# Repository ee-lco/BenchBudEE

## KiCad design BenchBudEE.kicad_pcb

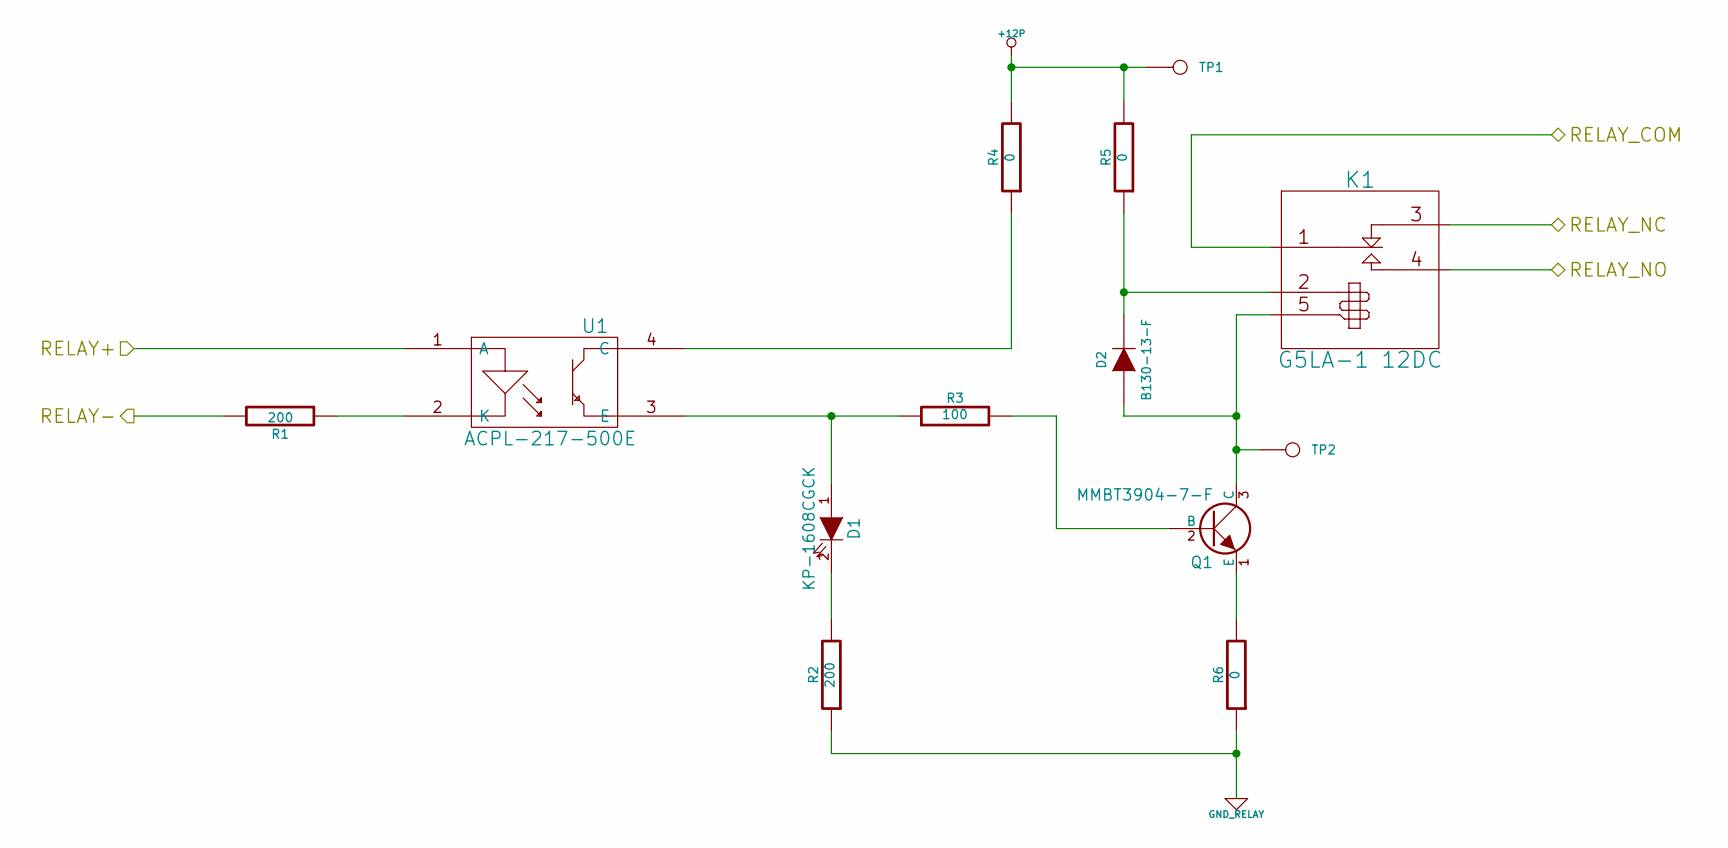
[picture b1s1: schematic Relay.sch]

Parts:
D1: KP-1608CGCK; LED-0603
D2: B130-13-F; Diode-SMA_Standard
K1: G5LA-1 12DC; TE-SPDT
Q1: MMBT3904-7-F; SOT23EBC; MFG Part Number MMBT3904-7-F
R1, R2: 200; SM0805
R3: 100; SM0805
R4, R5, R6: 0; SM0805
TP1: +12P; TestPointTH
TP2: RLY_LOW; TestPointTH
U1: ACPL-217-500E; 4-SMD; MFG Part Number LTV-816S

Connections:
+12P: R4.2, R5.2, TP1.1; also elsewhere on the board
/Arduino/RELAY+: U1.1 (A); also elsewhere on the board
/Arduino/RELAY-: R1.2; also elsewhere on the board
/Relay/RELAY_COM: K1.1 (COM); also elsewhere on the board
/Relay/RELAY_NC: K1.3 (NC); also elsewhere on the board
/Relay/RELAY_NO: K1.4 (NO); also elsewhere on the board
GND_RELAY: R2.1, R6.1; also elsewhere on the board
unnamed: D1.1 (A), R3.1, U1.3 (E)
unnamed: D1.2 (K), R2.2
unnamed: D2.1 (A), K1.5 (COIL-), Q1.3 (C), TP2.1
unnamed: D2.2 (K), K1.2 (COIL+), R5.1
unnamed: Q1.1 (E), R6.2
unnamed: Q1.2 (B), R3.2
unnamed: R1.1, U1.2 (K)
unnamed: R4.1, U1.4 (C)

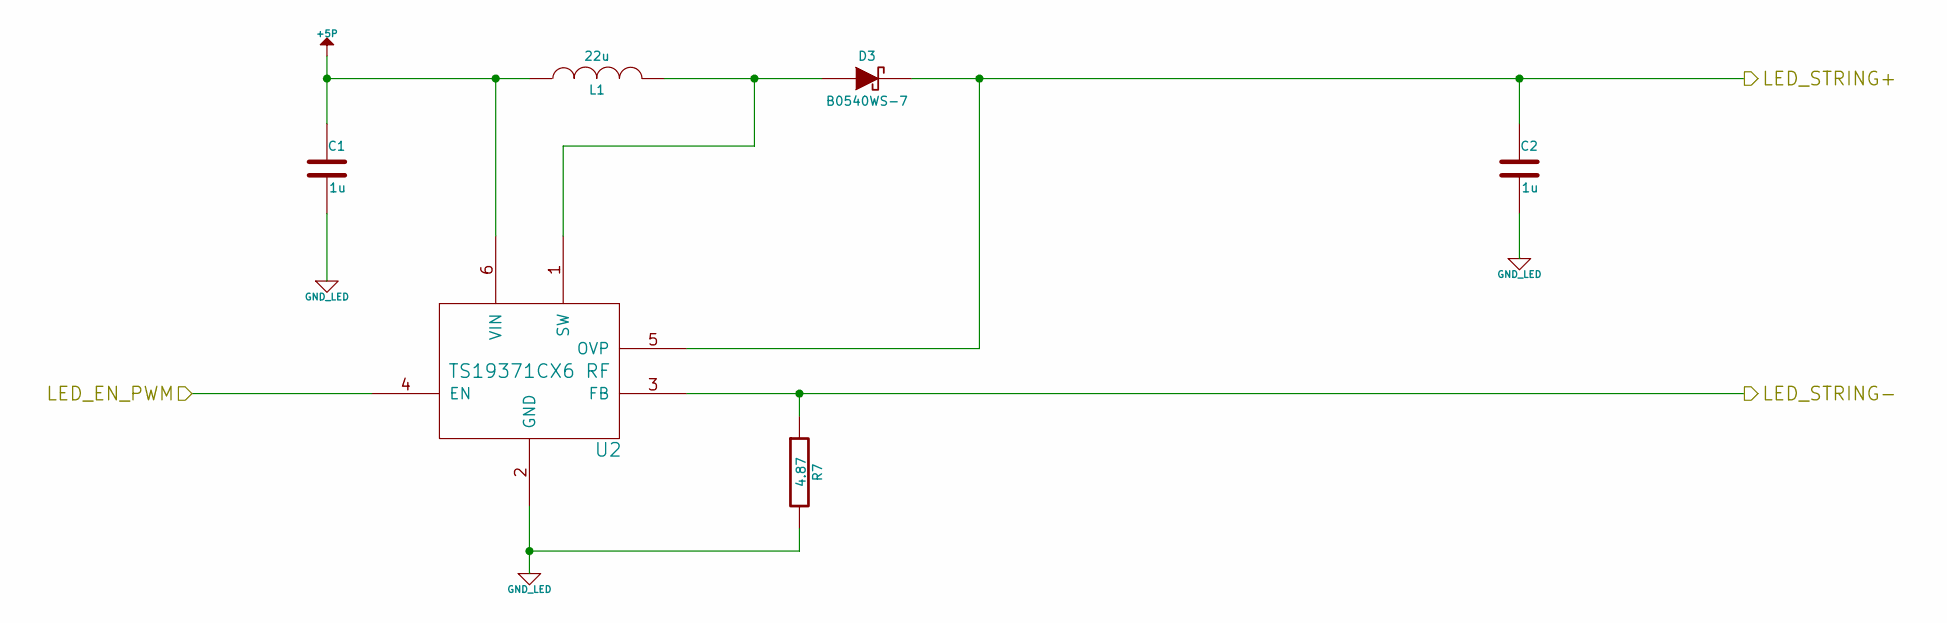
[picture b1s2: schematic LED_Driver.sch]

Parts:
C1, C2: 1u; c_0805
D3: B0540WS-7; SOD-323; MFG Part Number BO540WS-7
L1: 22u; NR4012; MFG Part Number NR4012T220M
R7: 4.87; SM0805
U2: TS19371CX6 RF; SOT23_6

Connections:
+5P: C1.1, L1.1, U2.6 (VIN); also elsewhere on the board
/Arduino/LED_EN_PWM: U2.4 (EN); also elsewhere on the board
/LED_Driver/LED_STRING+: C2.1, D3.2 (K), U2.5 (OVP); also elsewhere on the board
/LED_Driver/LED_STRING-: R7.1, U2.3 (FB); also elsewhere on the board
GND_LED: C1.2, C2.2, R7.2, U2.2 (GND); also elsewhere on the board
unnamed: D3.1 (A), L1.2, U2.1 (SW)

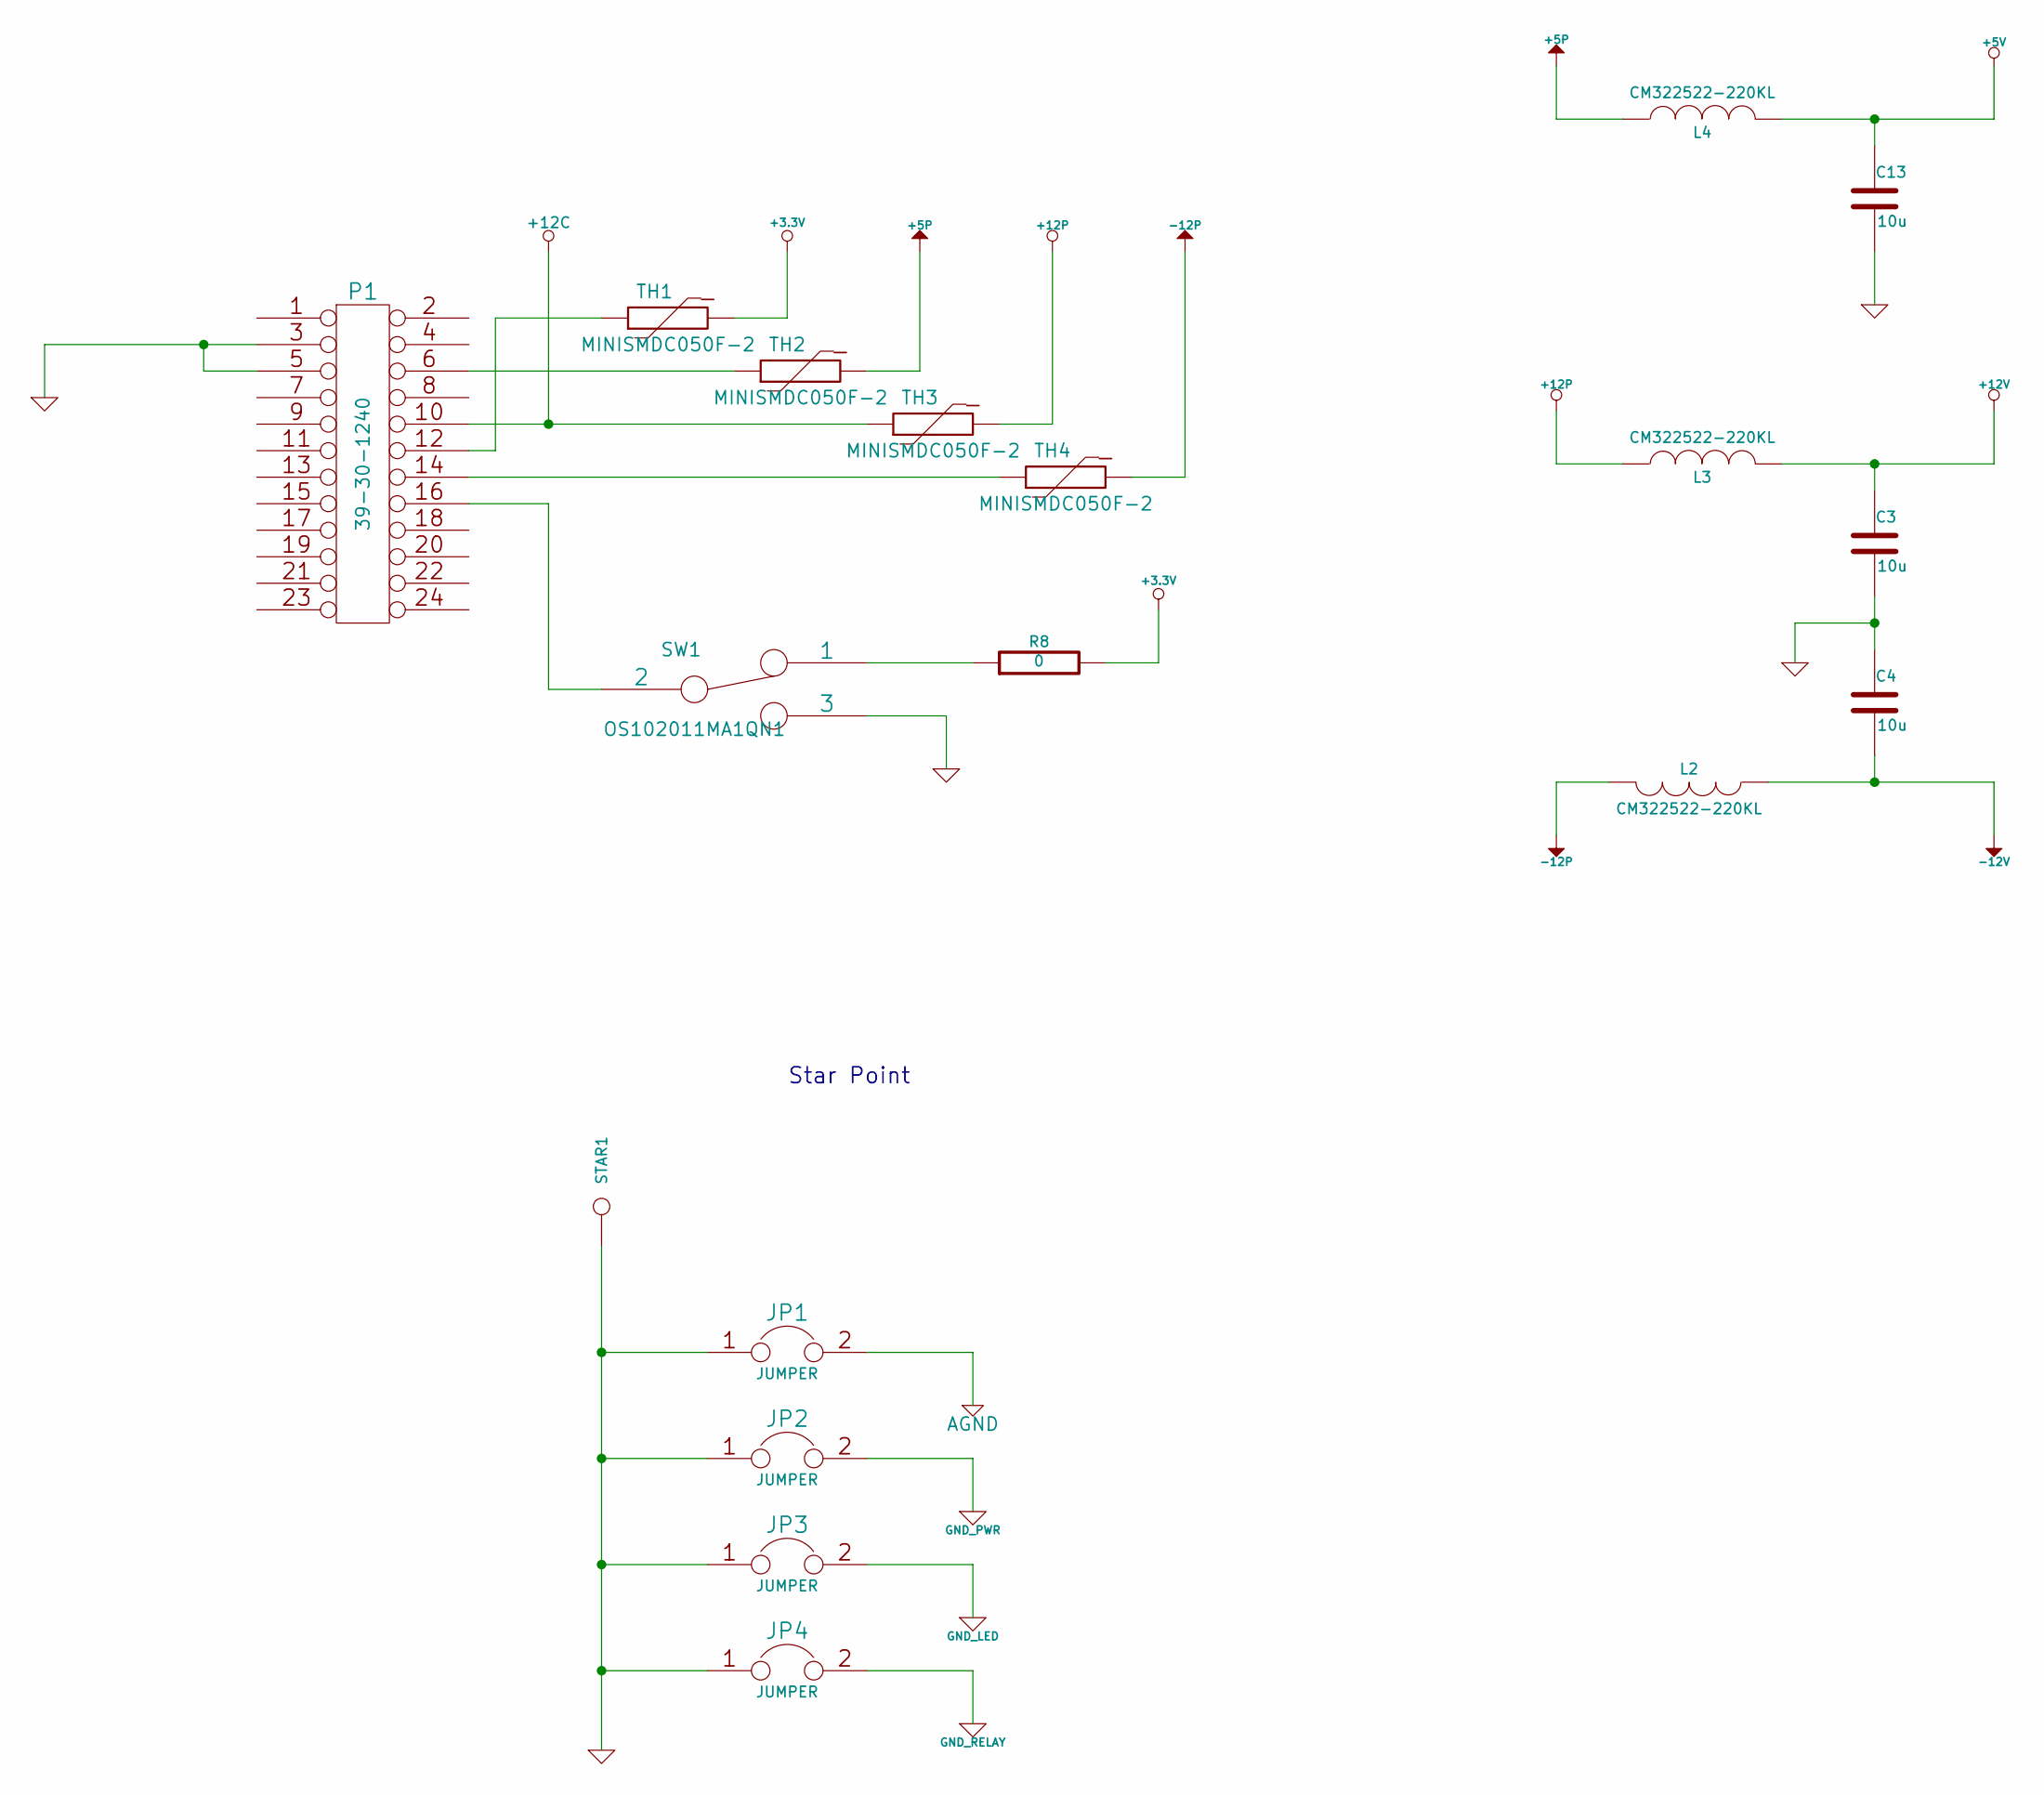
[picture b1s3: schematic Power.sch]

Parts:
C3, C4, C13: 10u; c_1206
JP1, JP2, JP3, JP4: JUMPER; GND_POINT
L2, L3, L4: CM322522-220KL; SM1210L
P1: 39-30-1240; ATX_Header; MFG Part Number 39-30-1240
R8: 0; SM0805
STAR1: CONN_1; 1pin
SW1: OS102011MA1QN1; BB_switch; MFG Part Number OS102011MA1QN1
TH1, TH2, TH3, TH4: MINISMDC050F-2; SM1812; MFG Part Number MINISMDC050F-2

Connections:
+3.3V: R8.2, TH1.2; also elsewhere on the board
+5P: L4.1, TH2.2; also elsewhere on the board
+5V: C13.1, L4.2; also elsewhere on the board
+12C: P1.10, TH3.1; also elsewhere on the board
+12P: L3.1, TH3.2; also elsewhere on the board
+12V: C3.1, L3.2; also elsewhere on the board
-12P: L2.2, TH4.2
-12V: C4.2, L2.1; also elsewhere on the board
AGND: JP1.2; also elsewhere on the board
GND: C3.2, C4.1, C13.2, JP1.1, JP2.1, JP3.1, JP4.1, P1.3, P1.5, STAR1.1, SW1.3; also elsewhere on the board
GND_LED: JP3.2; also elsewhere on the board
GND_PWR: JP2.2; also elsewhere on the board
GND_RELAY: JP4.2; also elsewhere on the board
unnamed: P1.6, TH2.1
unnamed: P1.12, TH1.1
unnamed: P1.14, TH4.1
unnamed: P1.16, SW1.2
unnamed: R8.1, SW1.1

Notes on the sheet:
Star Point

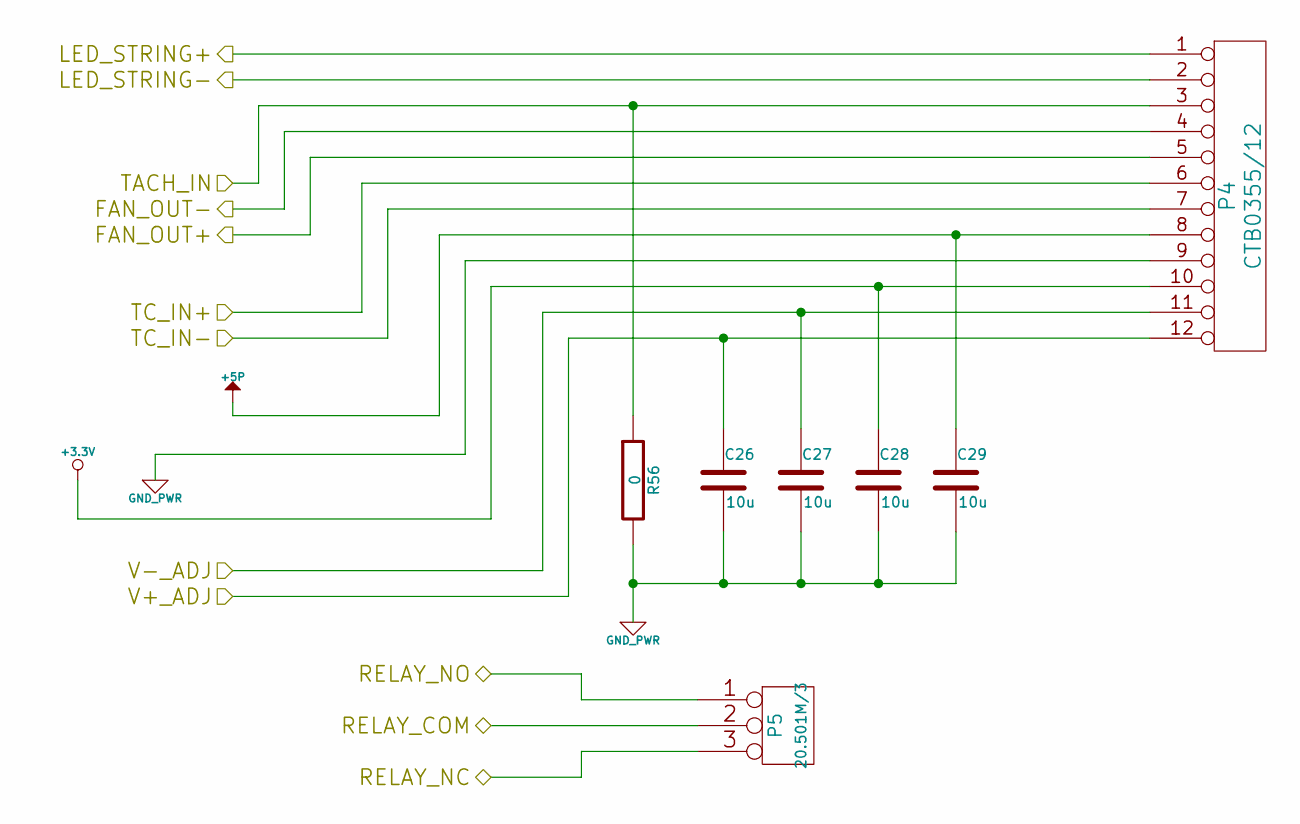
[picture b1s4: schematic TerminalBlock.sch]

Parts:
C26, C27, C28, C29: 10u; c_1210
P4: CTB0355/12; 12pinTB; MFG Part Number OSTTE120104
P5: 20.501M/3; 3pinTB; MFG Part Number 1935174
R56: 0; SM0805

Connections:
+3.3V: C28.1, P4.10; also elsewhere on the board
+5P: C29.1, P4.8; also elsewhere on the board
/Fan/FAN_OUT+: P4.5; also elsewhere on the board
/Fan/FAN_OUT-: P4.4; also elsewhere on the board
/Fan/TACH_IN: P4.3, R56.1; also elsewhere on the board
/LED_Driver/LED_STRING+: P4.1; also elsewhere on the board
/LED_Driver/LED_STRING-: P4.2; also elsewhere on the board
/PowerAdjustmentMonitor/V+_ADJ: C26.1, P4.12; also elsewhere on the board
/PowerAdjustmentMonitor/V-_ADJ: C27.1, P4.11; also elsewhere on the board
/Relay/RELAY_COM: P5.2 (PM); also elsewhere on the board
/Relay/RELAY_NC: P5.3; also elsewhere on the board
/Relay/RELAY_NO: P5.1; also elsewhere on the board
/TerminalBlock/TC_IN+: P4.6; also elsewhere on the board
/TerminalBlock/TC_IN-: P4.7; also elsewhere on the board
GND_PWR: C26.2, C27.2, C28.2, C29.2, P4.9, R56.2; also elsewhere on the board

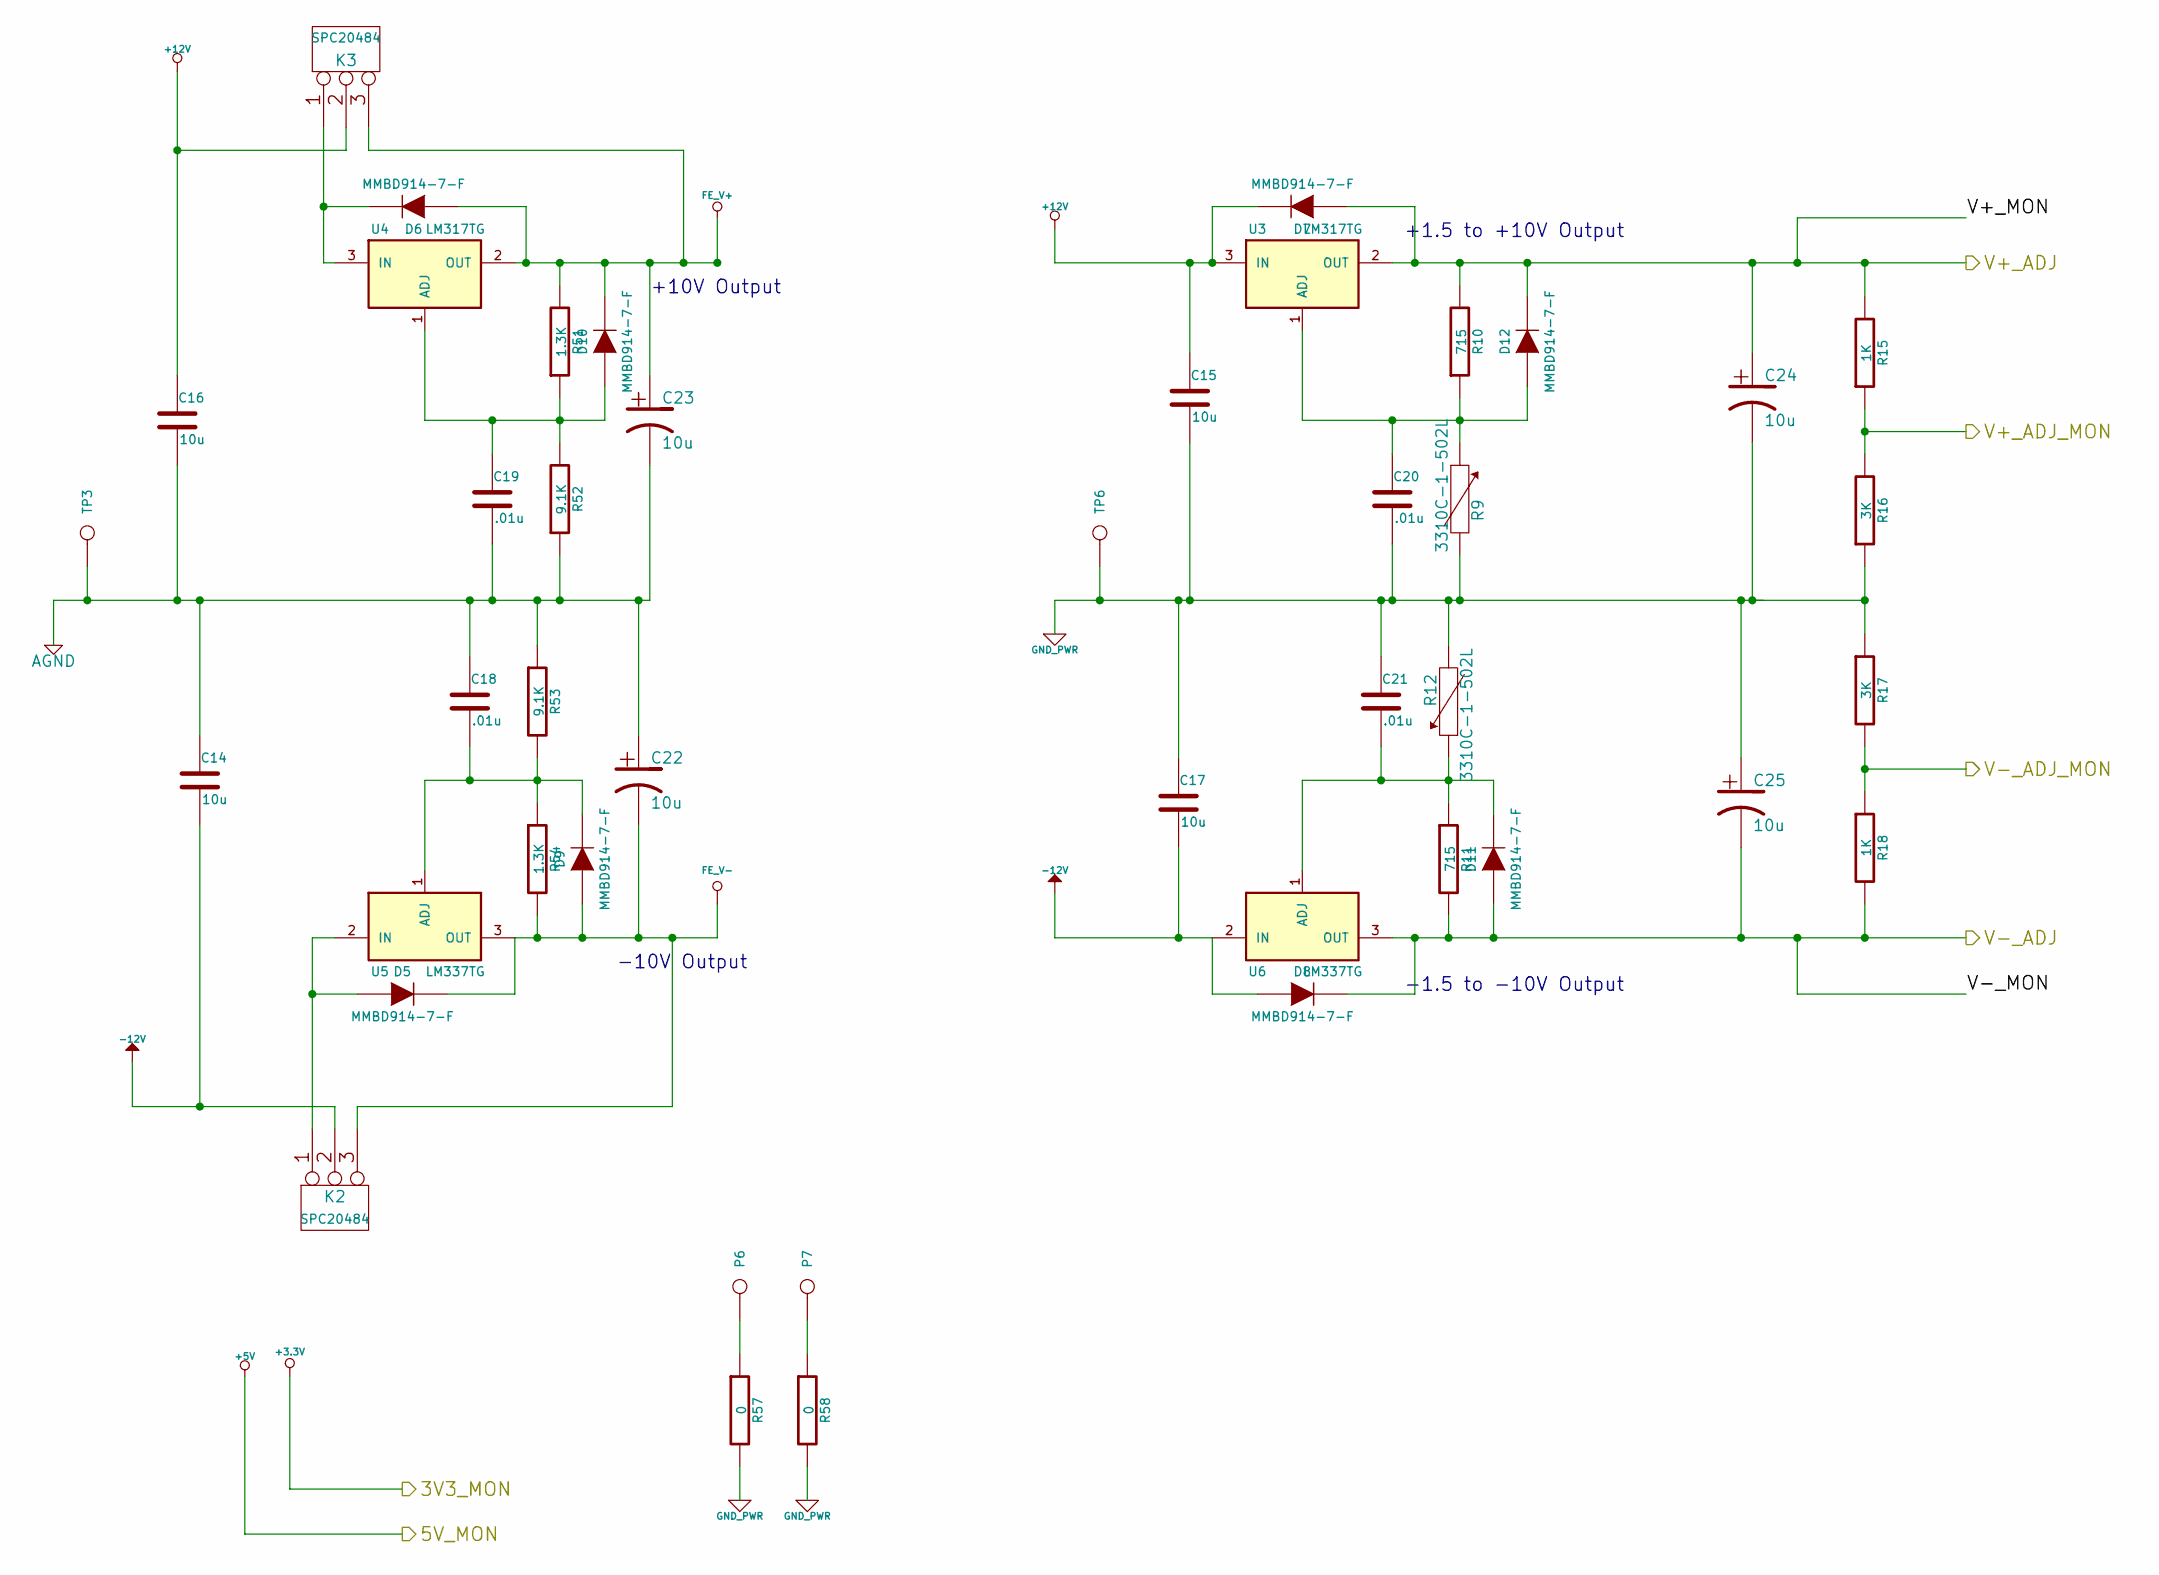
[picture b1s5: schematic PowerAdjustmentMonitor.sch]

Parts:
C14, C15, C16, C17, C22, C23, C24, C25: 10u; c_0805
C18, C19, C20, C21: .01u; c_0805
D5, D6, D7, D8, D9, D10, D11, D12: MMBD914-7-F; SOT23-DIODE; MFG Part Number MMBD914-7-F
K2, K3: SPC20484; Pin_Header_Straight_1x03
P6, P7: MC33282; V8508H
R9, R12: 3310C-1-502L; EVUE3K
R10, R11: 715; SM0805
R15, R18: 1K; SM0805
R16, R17: 3K; SM0805
R51, R54: 1.3K; SM0805
R52, R53: 9.1K; SM0805
R57, R58: 0; SM0805
TP3: AGND; TestPointTH
TP6: GND_PWR; TestPointTH
U3, U4: LM317TG; TO-220_Neutral123_Vertical
U5, U6: LM337TG; TO-220_Neutral123_Vertical

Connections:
+12V: C15.1, C16.1, D7.2 (K), K3.2 (PM), U3.3 (IN); also elsewhere on the board
-12V: C14.2, C17.2, D8.1 (A), K2.2 (PM), U6.2 (IN); also elsewhere on the board
/Arduino/V+_ADJ_MON: R15.1, R16.2; also elsewhere on the board
/Arduino/V-_ADJ_MON: R17.2, R18.1; also elsewhere on the board
/PowerAdjustmentMonitor/V+_ADJ: C24.1, D7.1 (A), D12.2 (K), R10.2, R15.2, U3.2 (OUT); also elsewhere on the board
/PowerAdjustmentMonitor/V-_ADJ: C25.2, D8.2 (K), D11.1 (A), R11.2, R18.2, U6.3 (OUT); also elsewhere on the board
AGND: C14.1, C16.2, C18.1, C19.2, C22.1, C23.2, R52.1, R53.1, TP3.1; also elsewhere on the board
FE_V+: C23.1, D6.1 (A), D10.2 (K), K3.3, R51.2, U4.2 (OUT); also elsewhere on the board
FE_V-: C22.2, D5.2 (K), D9.1 (A), K2.3, R54.2, U5.3 (OUT); also elsewhere on the board
GND_PWR: C15.2, C17.1, C20.2, C21.1, C24.2, C25.1, R9.2, R12.2, R16.1, R17.1, R57.2, R58.2, TP6.1; also elsewhere on the board
unnamed: C18.2, D9.2 (K), R53.2, R54.1, U5.1 (ADJ)
unnamed: C19.1, D10.1 (A), R51.1, R52.2, U4.1 (ADJ)
unnamed: C20.1, D12.1 (A), R9.1, R10.1, U3.1 (ADJ)
unnamed: C21.2, D11.2 (K), R11.1, R12.1, U6.1 (ADJ)
unnamed: D5.1 (A), K2.1, U5.2 (IN)
unnamed: D6.2 (K), K3.1, U4.3 (IN)
unnamed: P6.1, R57.1
unnamed: P7.1, R58.1

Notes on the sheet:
+10V Output
+1.5 to +10V Output
-1.5 to -10V Output
-10V Output

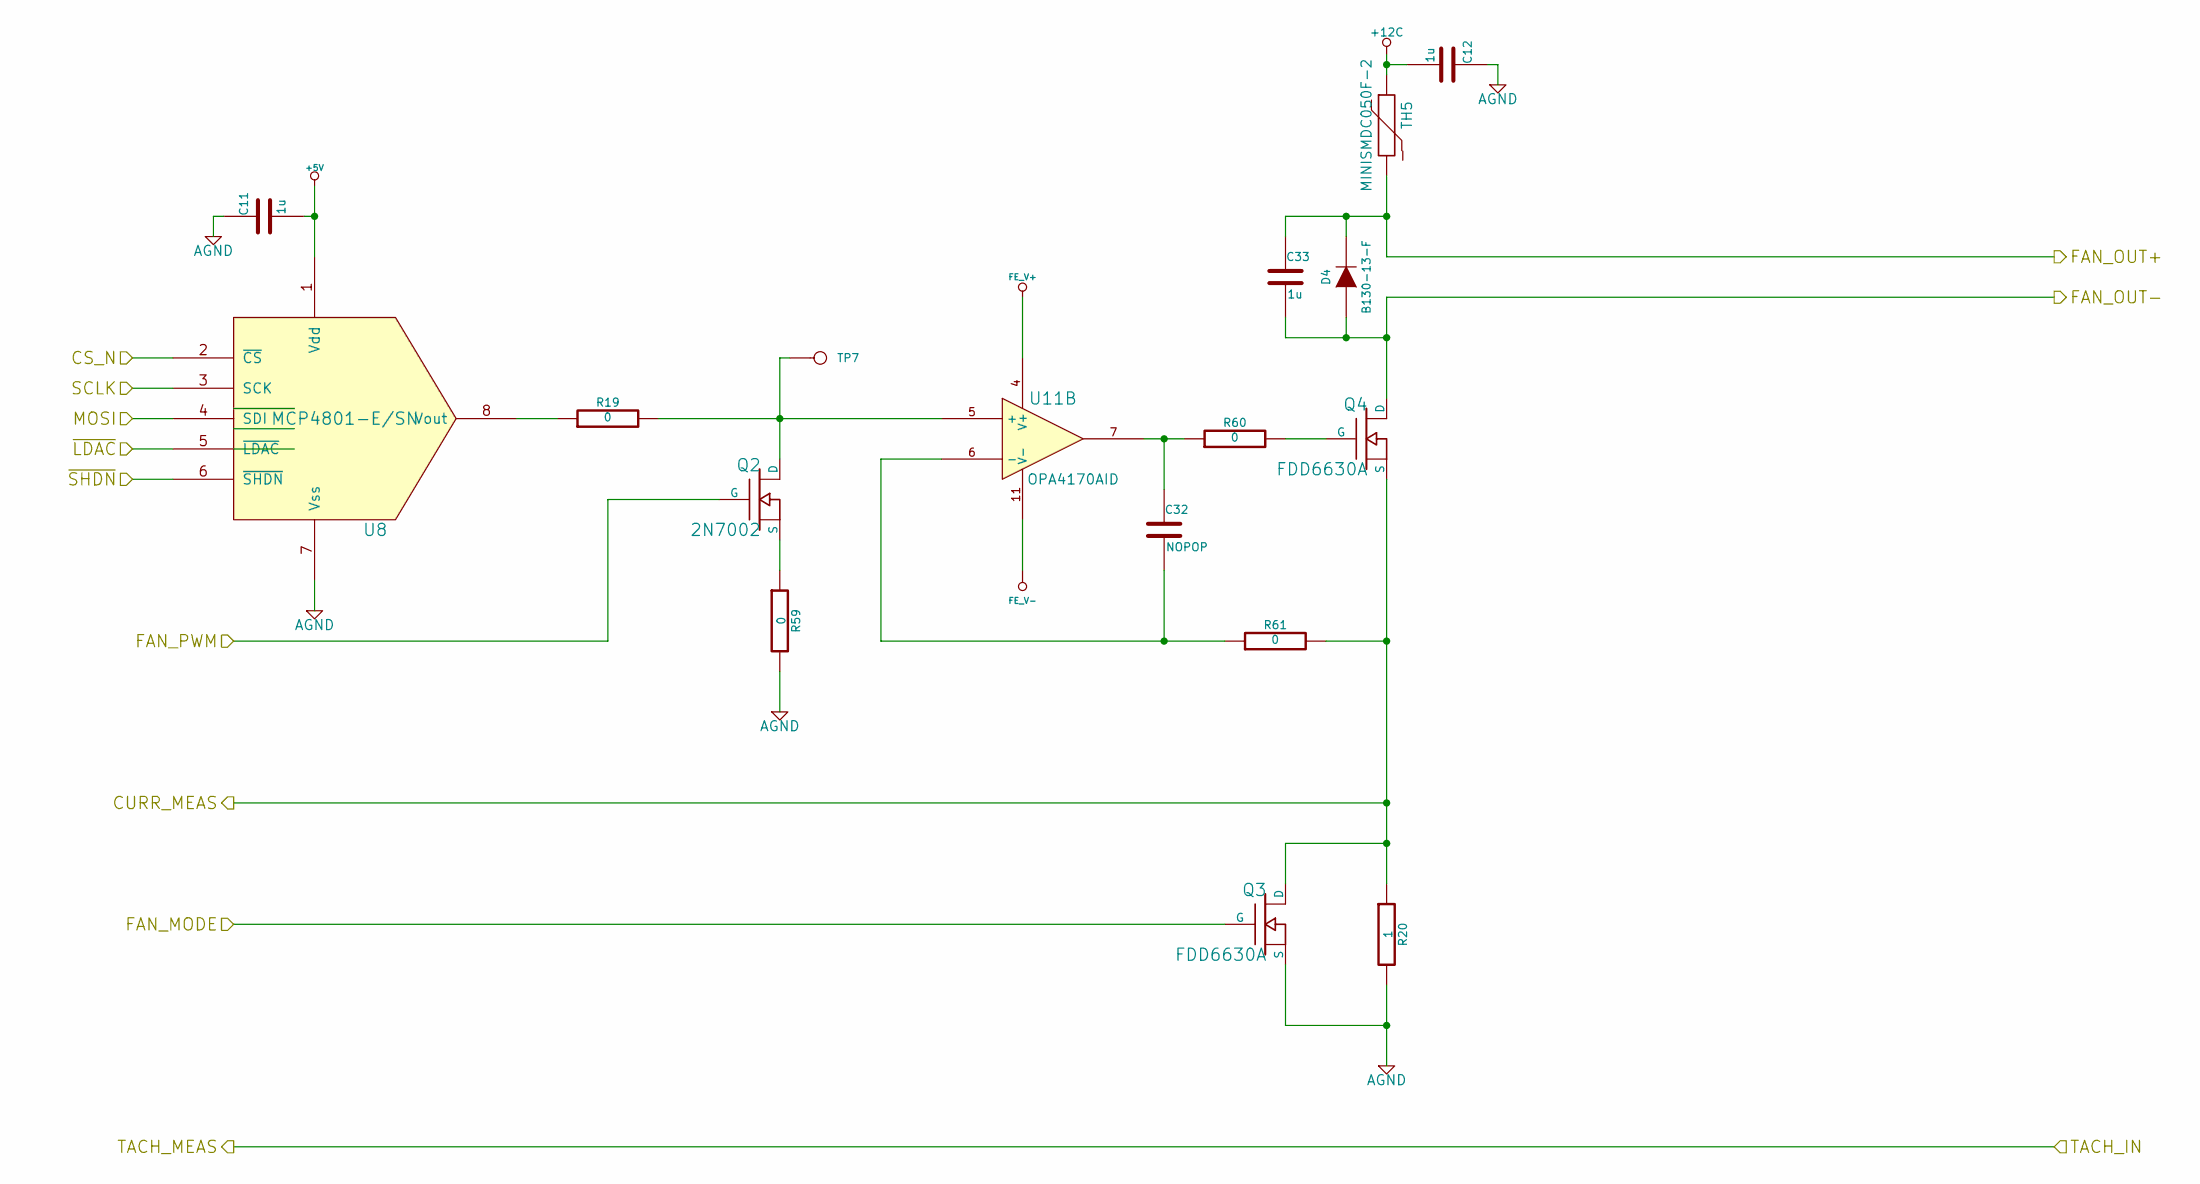
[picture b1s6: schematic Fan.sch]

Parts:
C11, C12, C33: 1u; c_0805
C32: NOPOP; c_0805
D4: B130-13-F; Diode-SMA_Standard; MFG Part Number B130-13-F
Q2: 2N7002; SOT23EBC; MFG Part Number DMN65D8L-7
Q3, Q4: FDD6630A; DPAK2; MFG Part Number AOD476
R19, R59, R60, R61: 0; SM0805
R20: 1; SM1206
TH5: MINISMDC050F-2; SM1812; MFG Part Number MINISMDC050F-2
TP7: DAC_OUT; TestPointTH
U8: MCP4801-E/SN; SO8N
U11: OPA4170AID; SO14E

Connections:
+5V: C11.2, U8.1 (Vdd); also elsewhere on the board
+12C: C12.2, TH5.1; also elsewhere on the board
/Arduino/CURR_MEAS: Q3.2 (D), Q4.3 (S), R20.1, R61.2; also elsewhere on the board
/Arduino/FAN_MODE: Q3.1 (G); also elsewhere on the board
/Arduino/FAN_PWM: Q2.1 (G); also elsewhere on the board
/Arduino/MOSI: U8.4 (SDI); also elsewhere on the board
/Arduino/SCLK: U8.3 (SCK); also elsewhere on the board
/Arduino/~LDAC: U8.5 (~LDAC); also elsewhere on the board
/Arduino/~SHDN: U8.6 (~SHDN); also elsewhere on the board
/Fan/CS_N: U8.2 (~CS); also elsewhere on the board
/Fan/FAN_OUT+: C33.1, D4.2 (K), TH5.2; also elsewhere on the board
/Fan/FAN_OUT-: C33.2, D4.1 (A), Q4.2 (D); also elsewhere on the board
AGND: C11.1, C12.1, Q3.3 (S), R20.2, R59.2, U8.7 (Vss); also elsewhere on the board
FE_V+: U11.4 (V+); also elsewhere on the board
FE_V-: U11.11 (V-); also elsewhere on the board
unnamed: C32.1, R60.1, U11.7
unnamed: C32.2, R61.1, U11.6 (-)
unnamed: Q2.2 (D), R19.2, TP7.1, U11.5 (+)
unnamed: Q2.3 (S), R59.1
unnamed: Q4.1 (G), R60.2
unnamed: R19.1, U8.8 (Vout)

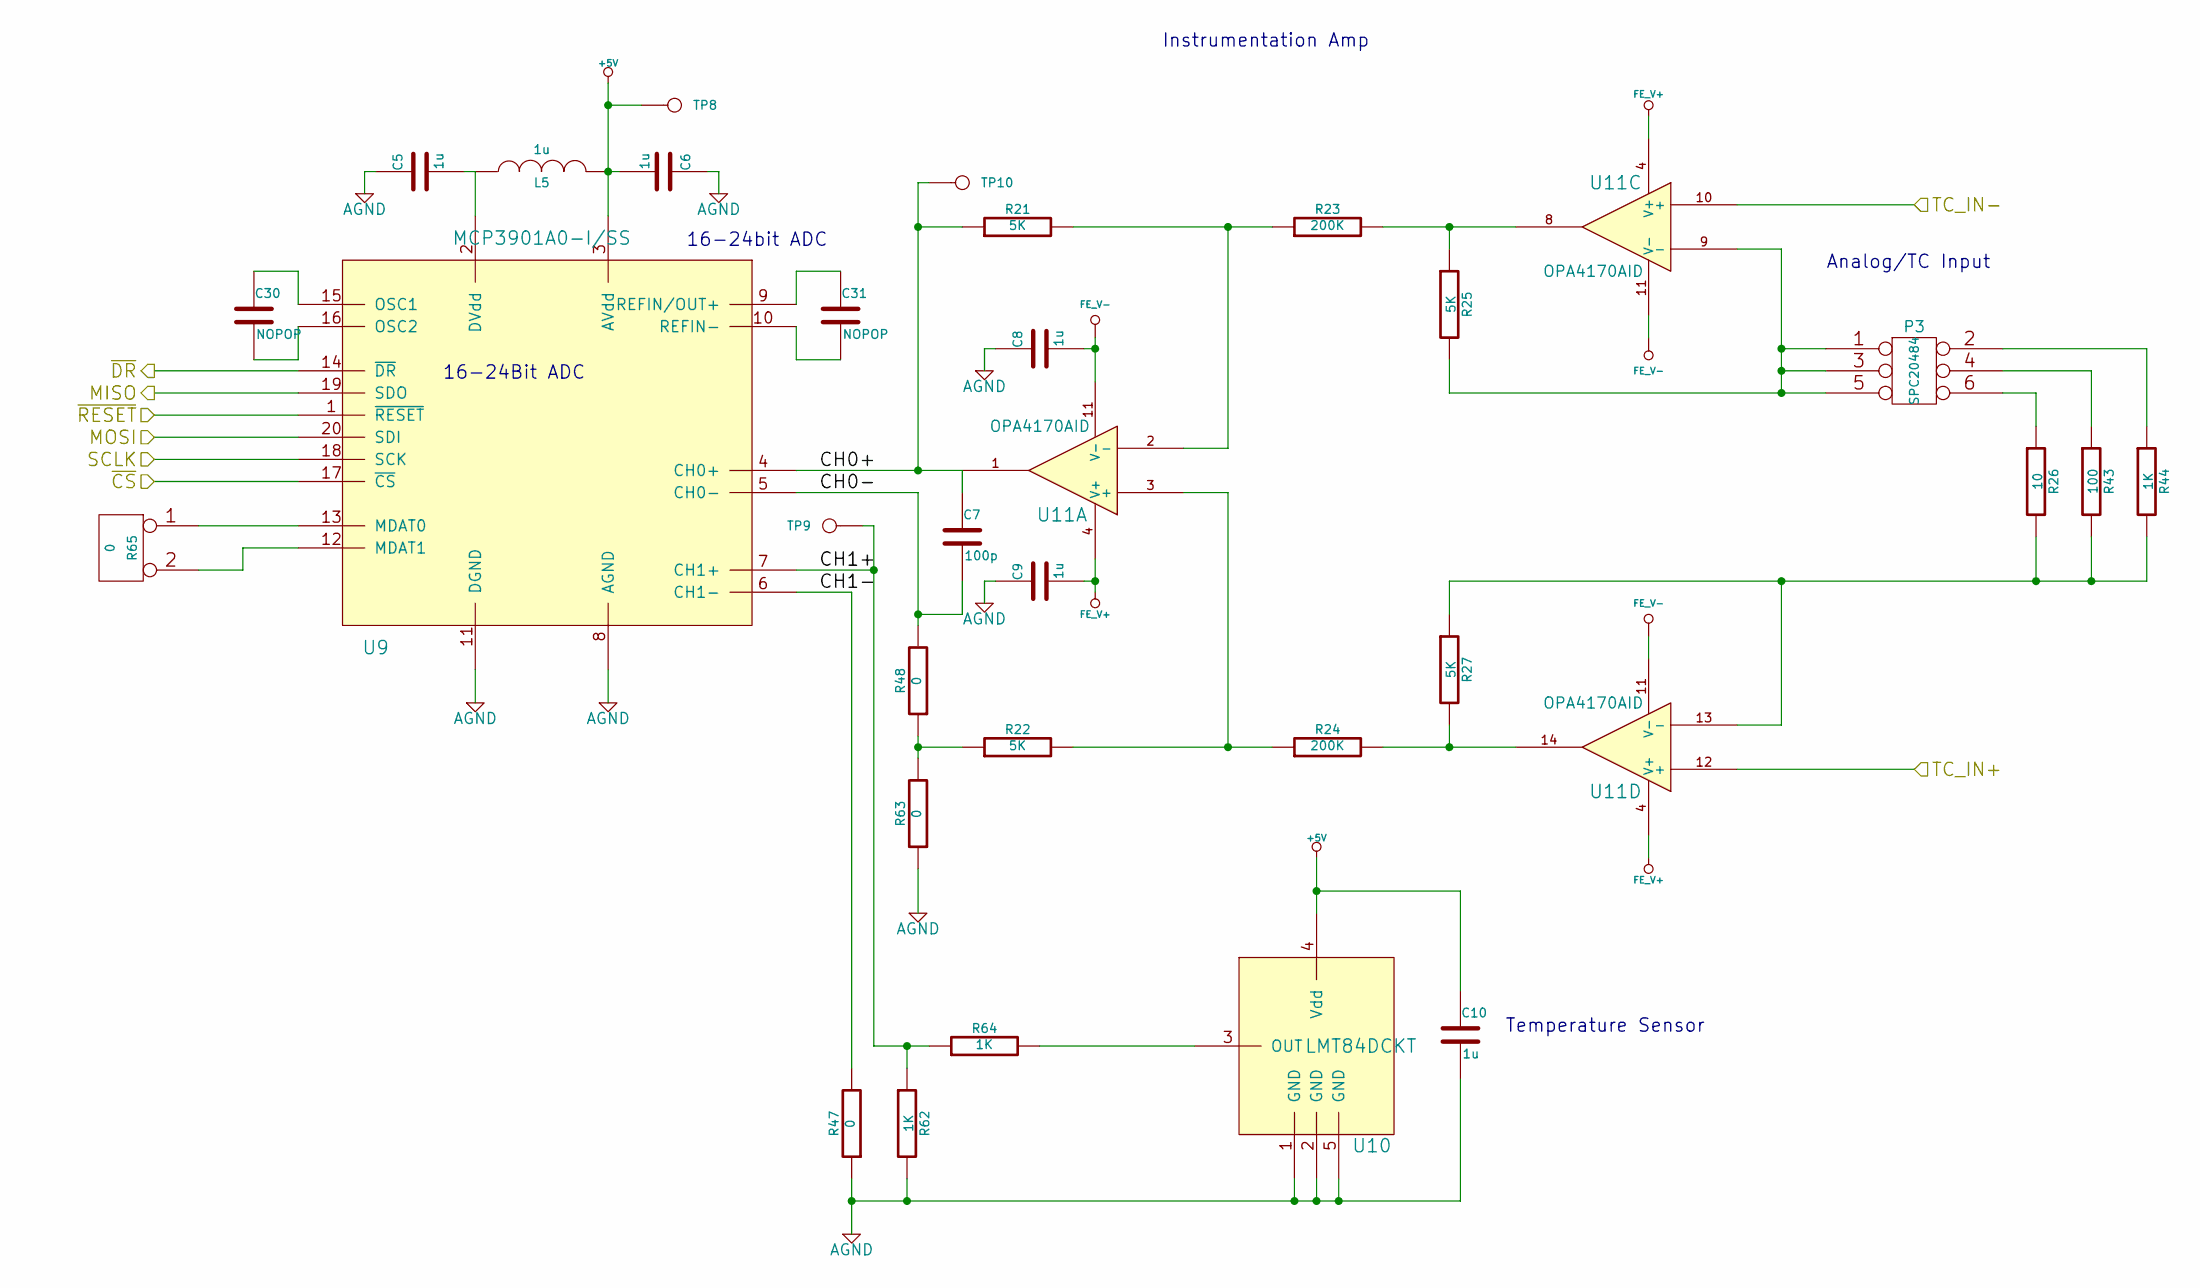
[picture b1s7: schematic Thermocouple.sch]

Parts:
C5, C6, C8, C9, C10: 1u; c_0805
C7: 100p; c_0805
C30, C31: NOPOP; c_0805
L5: 1u; SM0805
P3: SPC20484; Pin_Header_Straight_2x03
R21, R22: 5K; SM1206
R23, R24: 200K; SM1206
R25, R27: 5K; SM0805
R26: 10; SM0805
R43: 100; SM0805
R44, R62, R64: 1K; SM0805
R47, R48, R63, R65: 0; SM0805
TP8: +5V; TestPointTH
TP9: CH1+; TestPointTH
TP10: CH0+; TestPointTH
U9: MCP3901A0-I/SS; SSOP20
U10: LMT84DCKT; SOT353
U11: OPA4170AID; SO14E

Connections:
+5V: C6.2, C10.1, L5.2, TP8.1, U9.3 (AVdd), U10.4 (Vdd); also elsewhere on the board
/Arduino/MISO: U9.19 (SDO); also elsewhere on the board
/Arduino/MOSI: U9.20 (SDI); also elsewhere on the board
/Arduino/SCLK: U9.18 (SCK); also elsewhere on the board
/Arduino/~ADC_CS: U9.17 (~CS); also elsewhere on the board
/Arduino/~DR: U9.14 (~DR); also elsewhere on the board
/Arduino/~RESET: U9.1 (~RESET); also elsewhere on the board
/TerminalBlock/TC_IN+: U11.12 (+); also elsewhere on the board
/TerminalBlock/TC_IN-: U11.10 (+); also elsewhere on the board
/Thermocouple/CH0+: C7.1, R21.1, TP10.1, U9.4 (CH0+), U11.1
/Thermocouple/CH0-: C7.2, R48.2, U9.5 (CH0-)
/Thermocouple/CH1+: R62.1, R64.1, TP9.1, U9.7 (CH1+)
/Thermocouple/CH1-: R47.2, U9.6 (CH1-)
AGND: C5.1, C6.1, C8.1, C9.1, C10.2, R47.1, R62.2, R63.1, U9.8 (AGND), U9.11 (DGND), U10.1 (GND), U10.2 (GND), U10.5 (GND); also elsewhere on the board
FE_V+: C9.2, U11.4 (V+); also elsewhere on the board
FE_V-: C8.2, U11.11 (V-); also elsewhere on the board
unnamed: C5.2, L5.1, U9.2 (DVdd)
unnamed: C30.1, U9.15 (OSC1)
unnamed: C30.2, U9.16 (OSC2)
unnamed: C31.1, U9.9 (REFIN/OUT+)
unnamed: C31.2, U9.10 (REFIN-)
unnamed: P3.1, P3.3, P3.5, R25.2, U11.9 (-)
unnamed: P3.2, R44.1
unnamed: P3.4, R43.1
unnamed: P3.6, R26.1
unnamed: R21.2, R23.1, U11.2 (-)
unnamed: R22.1, R48.1, R63.2
unnamed: R22.2, R24.1, U11.3 (+)
unnamed: R23.2, R25.1, U11.8
unnamed: R24.2, R27.2, U11.14
unnamed: R26.2, R27.1, R43.2, R44.2, U11.13 (-)
unnamed: R64.2, U10.3 (OUT)
unnamed: R65.1, U9.13 (MDAT0)
unnamed: R65.2 (PM), U9.12 (MDAT1)

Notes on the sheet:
Analog/TC Input
Instrumentation Amp
16-24Bit ADC
Temperature Sensor
16-24bit ADC
